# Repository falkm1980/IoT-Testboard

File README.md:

# IoT-Testboard
IoT-Testboard for Raspberry pi and ESP8266

In order to get the IoT-Evaluation board running you need a recent image of Raspian-Linux.
https://www.raspberrypi.org/downloads/raspbian/

Furthermore you need to install a few more libraries.

## Wiring Pi
git clone https://github.com/WiringPi/WiringPi

./build

## Adafruit_Python GPIO Library
git clone https://github.com/adafruit/Adafruit_Python_GPIO

## Adafruit ILI9341 Display Library
git clone https://github.com/adafruit/Adafruit_Python_ILI9341

## RC-Switch (Radio outlets)
git clone https://github.com/r10r/rcswitch-pi

make

## DHT 11/22 Temp/Humidity sensor
git clone https://github.com/adafruit/Adafruit_Python_DHT

## NeoPixel WS2812:
sudo apt-get update

sudo apt-get install icons

sudo apt-get install scons

sudo apt-get install swig

sudo apt-get install build-essential python-dev unzip wget 

wget https://github.com/jgarff/rpi_ws281x/archive/master.zip && unzip master.zip && cd rpi_ws281x-master && sudo scons && cd python && 
sudo python setup.py install

## optional Div. Python libs:
sudo pip install pytz (for timezone calculation)

## Optional: Node.JS latest version
sudo wget -O - https://raw.githubusercontent.com/audstanley/NodeJs-Raspberry-Pi/master/Install-Node.sh | sudo bash;
node -v;

## Mqtt ##
Install MQTT Broker: sudo apt-get install moquitto

Install MQTT Pyhon lib: pip install paho-mqtt

see also: https://www.dinotools.de/2015/04/12/mqtt-mit-python-nutzen/

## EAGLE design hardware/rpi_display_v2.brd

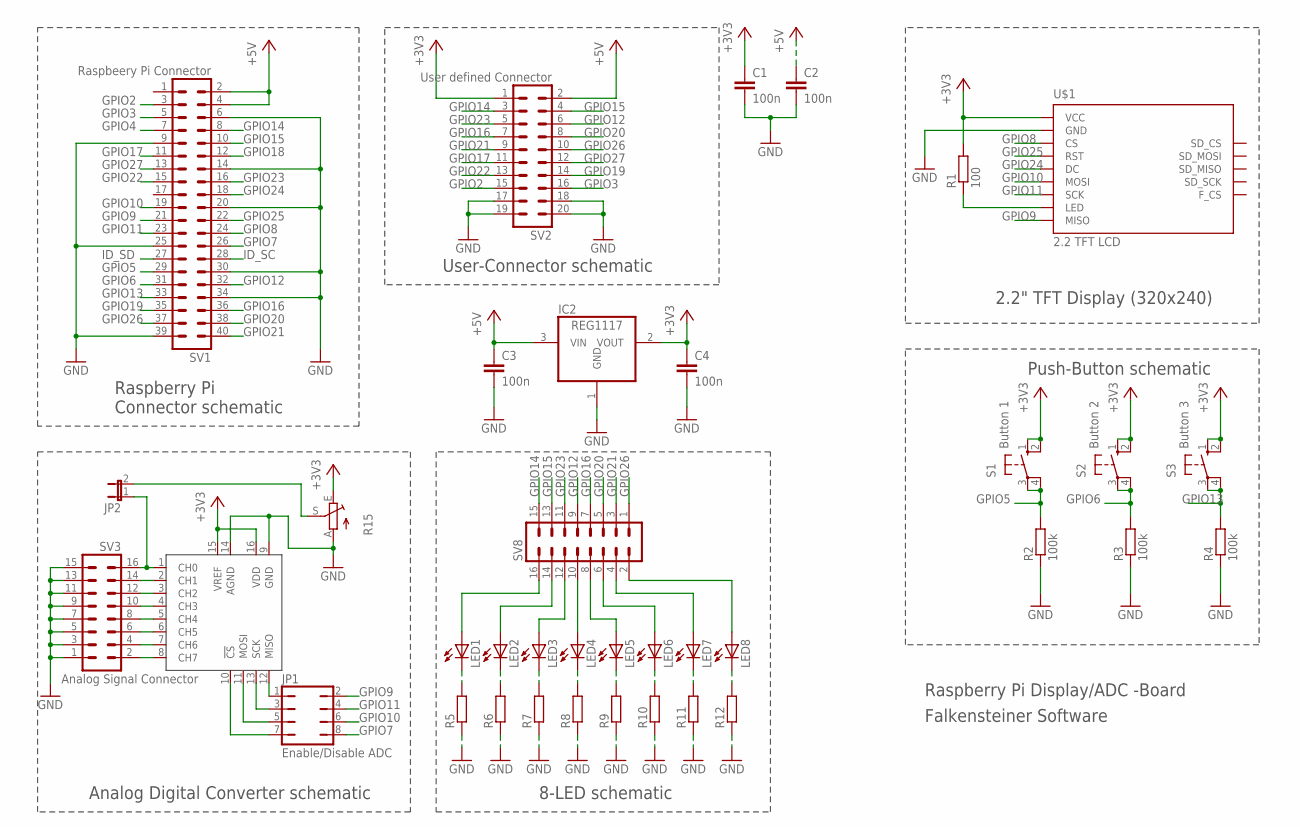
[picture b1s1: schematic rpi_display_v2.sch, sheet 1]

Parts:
C1, C2, C3, C4: 100n; C1206
IC1: MCP3008P; DIL16
IC2: REG1117; SOT223
JP1: Enable/Disable ADC; JP4Q
JP2: JP1E; JP1
LED1, LED2, LED3, LED4, LED5, LED6, LED7, LED8: LEDSML1206; SML1206
R1: 100; R1206
R2, R3, R4: 100k; R1206
R5, R6, R7, R8, R9, R10, R11, R12: R-EU_R1206; R1206
R15: TRIM_EU-CA6V; CA6V
S1: Button 1; B3F-10XX
S2: Button 2; B3F-10XX
S3: Button 3; B3F-10XX
SV1: Raspbeery Pi Connector; MA20-2
SV2: User defined Connector; MA10-2
SV3: Analog Signal Connector; MA08-2
SV8: MA08-2
U$1: 2.2_TFT_LCD

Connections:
+3V3: C1.1, C4.1, IC1.15 (VREF), IC1.16 (VDD), IC2.2 (VOUT), R1.2, R15.E, S1.1 (S), S1.2 (S1), S2.1 (S), S2.2 (S1), S3.1 (S), S3.2 (S1), SV2.1, U$1.VCC; also elsewhere on the board
+5V: C2.1, C3.1, IC2.3 (VIN), SV1.2, SV1.4, SV2.2; also elsewhere on the board
GND: C1.2, C2.2, C3.2, C4.2, IC1.9 (GND), IC1.14 (AGND), IC2.1 (GND), R2.1, R3.1, R4.1, R5.1, R6.1, R7.1, R8.1, R9.1, R10.1, R11.1, R12.1, R15.A, SV1.6, SV1.9, SV1.14, SV1.20, SV1.25, SV1.30, SV1.34, SV1.39, SV2.17, SV2.18, SV2.19, SV2.20, SV3.1, SV3.3, SV3.5, SV3.7, SV3.9, SV3.11, SV3.13, SV3.15, U$1.GND; also elsewhere on the board
GPIO2: SV1.3, SV2.15
GPIO3: SV1.5, SV2.16
GPIO4: SV1.7; also elsewhere on the board
GPIO5: R2.2, S1.3, S1.4 (P1), SV1.29
GPIO6: R3.2, S2.3, S2.4 (P1), SV1.31
GPIO7: JP1.8, SV1.26
GPIO8: SV1.24, U$1.CS
GPIO9: JP1.2, SV1.21, U$1.MISO
GPIO10: JP1.6, SV1.19, U$1.MOSI
GPIO11: JP1.4, SV1.23, U$1.SCK
GPIO12: SV1.32, SV2.6, SV8.9
GPIO13: R4.2, S3.3, S3.4 (P1), SV1.33
GPIO14: SV1.8, SV2.3, SV8.15
GPIO15: SV1.10, SV2.4, SV8.13
GPIO16: SV1.36, SV2.7, SV8.7
GPIO17: SV1.11, SV2.11; also elsewhere on the board
GPIO18: SV1.12; also elsewhere on the board
GPIO19: SV1.35, SV2.14
GPIO20: SV1.38, SV2.8, SV8.5
GPIO21: SV1.40, SV2.9, SV8.3
GPIO22: SV1.15, SV2.13; also elsewhere on the board
GPIO23: SV1.16, SV2.5, SV8.11
GPIO24: SV1.18, U$1.DC
GPIO25: SV1.22, U$1.RST
GPIO26: SV1.37, SV2.10, SV8.1
GPIO27: SV1.13, SV2.12; also elsewhere on the board
ID_SC: SV1.28
ID_SD: SV1.27
unnamed: R1.1, U$1.LED
unnamed: IC1.12 (MISO), JP1.1
unnamed: IC1.13 (SCK), JP1.3
unnamed: IC1.11 (MOSI), JP1.5
unnamed: IC1.10 (!CS), JP1.7
unnamed: IC1.1 (CH0), JP2.1, SV3.16
unnamed: IC1.2 (CH1), SV3.14
unnamed: IC1.3 (CH2), SV3.12
unnamed: IC1.4 (CH3), SV3.10
unnamed: IC1.5 (CH4), SV3.8
unnamed: IC1.6 (CH5), SV3.6
unnamed: IC1.7 (CH6), SV3.4
unnamed: IC1.8 (CH7), SV3.2
unnamed: LED1.A, SV8.16
unnamed: LED1.C, R5.2
unnamed: LED2.A, SV8.14
unnamed: LED2.C, R6.2
unnamed: LED3.A, SV8.12
unnamed: LED3.C, R7.2
unnamed: LED4.A, SV8.10
unnamed: LED4.C, R8.2
unnamed: LED5.A, SV8.8
unnamed: LED5.C, R9.2
unnamed: LED6.A, SV8.6
unnamed: LED6.C, R10.2
unnamed: LED7.A, SV8.4
unnamed: LED7.C, R11.2
unnamed: LED8.A, SV8.2
unnamed: LED8.C, R12.2
unnamed: JP2.2, R15.S

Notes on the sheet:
Raspberry Pi Display/ADC -Board
Falkensteiner Software
Push-Button schematic
User-Connector schematic
Raspberry Pi Connector schematic
Analog Digital Converter schematic
8-LED schematic
2.2" TFT Display (320x240)

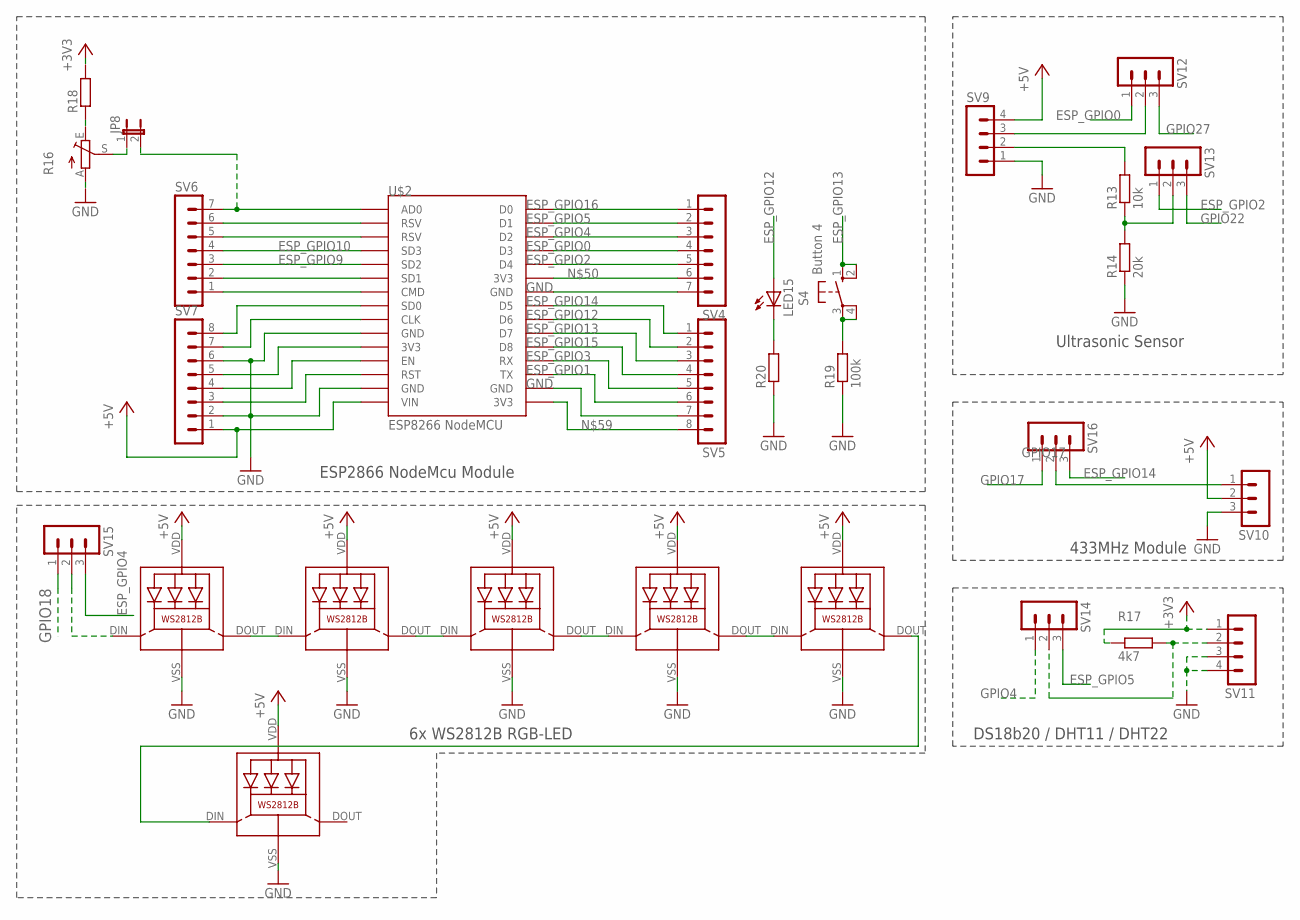
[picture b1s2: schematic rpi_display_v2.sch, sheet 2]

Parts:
JP8: JP1E; JP1
LED9, LED10, LED11, LED12, LED13, LED14: WS2812B
LED15: LEDSML1206; SML1206
R13: 10k; R1206
R14: 20k; R1206
R16: TRIM_EU-CA6V; CA6V
R17: 4k7; R1206
R18, R20: R-EU_R1206; R1206
R19: 100k; R1206
S4: Button 4; B3F-10XX
SV4, SV6: MA07-1
SV5, SV7: MA08-1
SV9, SV11: MA04-1
SV10, SV12, SV13, SV14, SV15, SV16: MA03-1
U$2: ESP8266 NodeMCU; ESP12E_DEVKIT

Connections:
+3V3: R17.1, R18.2, SV11.1; also elsewhere on the board
+5V: LED9.VDD, LED10.VDD, LED11.VDD, LED12.VDD, LED13.VDD, LED14.VDD, SV7.1, SV9.4, SV10.2, U$2.VIN; also elsewhere on the board
ESP_GPIO0: SV4.4, SV12.1, U$2.D3
ESP_GPIO1: SV5.6, U$2.TX
ESP_GPIO2: SV4.5, SV13.1, U$2.D4
ESP_GPIO3: SV5.5, U$2.RX
ESP_GPIO4: SV4.3, SV15.3, U$2.D2
ESP_GPIO5: SV4.2, SV14.3, U$2.D1
ESP_GPIO9: SV6.3, U$2.SD2
ESP_GPIO10: SV6.4, U$2.SD3
ESP_GPIO12: LED15.A, SV5.2, U$2.D6
ESP_GPIO13: S4.1 (S), S4.2 (S1), SV5.3, U$2.D7
ESP_GPIO14: SV5.1, SV16.3, U$2.D5
ESP_GPIO15: SV5.4, U$2.D8
ESP_GPIO16: SV4.1, U$2.D0
GND: LED9.VSS (GND), LED10.VSS (GND), LED11.VSS (GND), LED12.VSS (GND), LED13.VSS (GND), LED14.VSS (GND), R14.1, R16.A, R19.1, R20.1, SV4.7, SV5.7, SV7.2, SV7.6, SV9.1, SV10.3, SV11.3, SV11.4, U$2.GND@0 (GND), U$2.GND@1 (GND), U$2.GND@2 (GND), U$2.GND@3 (GND); also elsewhere on the board
GPIO4: SV14.1; also elsewhere on the board
GPIO17: SV16.1; also elsewhere on the board
GPIO18: SV15.1; also elsewhere on the board
GPIO22: SV13.3; also elsewhere on the board
GPIO27: SV12.3; also elsewhere on the board
unnamed: JP8.2, SV6.7, U$2.AD0
unnamed: SV6.6, U$2.RSV@0 (RSV)
unnamed: SV6.5, U$2.RSV@1 (RSV)
unnamed: LED15.C, R20.2
unnamed: R19.2, S4.3, S4.4 (P1)
unnamed: SV6.2, U$2.SD1
unnamed: SV6.1, U$2.CMD
unnamed: SV7.8, U$2.SD0
unnamed: SV7.7, U$2.CLK
unnamed: LED13.DOUT (DO), LED14.DIN (DI)
unnamed: SV7.5, U$2.3V3@0 (3V3)
unnamed: SV7.4, U$2.EN
unnamed: SV7.3, U$2.RST
unnamed: LED9.DOUT (DO), LED10.DIN (DI)
unnamed: LED10.DOUT (DO), LED11.DIN (DI)
unnamed: SV4.6, U$2.3V3@1 (3V3)
unnamed: SV5.8, U$2.3V3@2 (3V3)
unnamed: LED11.DOUT (DO), LED12.DIN (DI)
unnamed: LED12.DOUT (DO), LED13.DIN (DI)
unnamed: R13.1, R14.2, SV13.2
unnamed: R13.2, SV9.2
unnamed: SV9.3, SV12.2
unnamed: SV10.1, SV16.2
unnamed: LED9.DIN (DI), SV15.2
unnamed: R17.2, SV11.2, SV14.2
unnamed: R16.E, R18.1
unnamed: JP8.1, R16.S

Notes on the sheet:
Ultrasonic Sensor
433MHz Module
DS18b20 / DHT11 / DHT22
6x WS2812B RGB-LED
ESP2866 NodeMcu Module

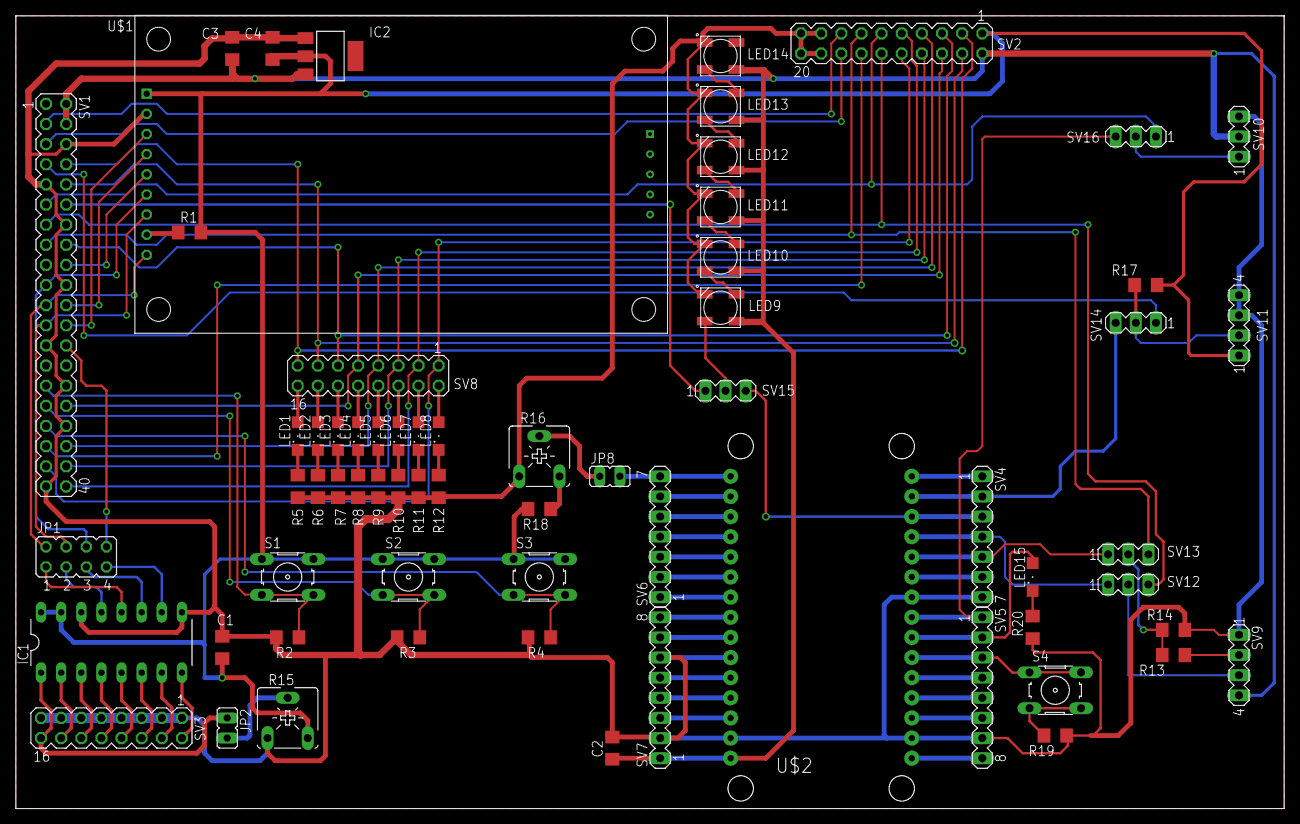
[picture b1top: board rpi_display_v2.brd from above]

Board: 2 copper layers, 160.0 x 100.0 mm, 66 parts (0 on the bottom side), 99 nets.

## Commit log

2017-12-05 added EagleFiles and Schematic PDF
2017-12-15 ESP8266 section added
2017-12-15 update text
2017-12-15 Post/Get api for DHT11-Data added
2018-02-02 added max_speed_hz
    added max_speed_hz in Open function. Otherwise the ADC doesn't work with the latest raspbian image
2018-02-06 print update beacuse of Python3
2018-02-06 logo added
2018-02-06 Python3 update
2018-02-06 Python3 Distance Sensor file
2018-02-06 DispOnlyTest update without DHT1 sensor
2018-02-06 font changed
2018-02-25 added ShowIpDisplay script
2019-05-21 test
